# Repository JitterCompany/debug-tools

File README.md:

# Debug Tools for Embedded Development

KiCad projects for the small debug, programming and test boards used across Jitter
projects. Each board has its own folder; manufacturing files are in `production/`.

## Debug adapters

Most Jitter boards expose a single 6-pin
[Würth REDFIT IDC SKEDD](https://www.we-online.com/en/components/products/WST_IDC_PRE_PRESSED_CONNECTOR)
footprint that carries both **SWD and a UART**. SKEDD connectors press straight into
plated holes, so the target board needs no mating connector. The adapters below
convert a debug probe's native header to that 6-pin cable.

| Board | Probe side | Notes |
|---|---|---|
| [BMP-REDFit-adapter](BMP-REDFit-adapter) | Black Magic Probe: standard 10-pin 1.27 mm Arm Cortex Debug header + 4-pin PicoBlade UART | the 10-pin is the common Arm/MIPI-10 JTAG/SWD pinout, so most Cortex probes fit (UART via the separate PicoBlade) |
| [HSprobe-REDFit-adapter](HSprobe-REDFit-adapter) | [hs-probe](https://github.com/probe-rs/hs-probe): 14-pin 1.27 mm STDC14 | STDC14 is ST's STLINK-V3 connector (Arm 10-pin on pins 3–12, UART on 13/14), so STLINK-V3 should fit too |
| [JLink-REDFit-adapter](JLink-REDFit-adapter) | J-Link: standard 20-pin 2.54 mm Arm JTAG header + 4-pin PicoBlade UART | other 20-pin tools give SWD; UART on pins 5/17 is J-Link VCOM specific (else use the PicoBlade) |

### Other adapters

| Board | Purpose |
|---|---|
| [JLink-to-TC2030-IDC__microchip](JLink-to-TC2030-IDC__microchip) | J-Link 20-pin to a Tag-Connect TC2030-IDC with Microchip's pinout |
| [jtag-swd](jtag-swd) | 10-pin Cortex SWD header broken out to 2.54 mm pin headers |

## Misc tools

| Board | Purpose |
|---|---|
| [USBSwitch](USBSwitch) | USB-A / micro-USB passthrough with jumpers to disconnect the data lines and select VBUS from the host or an external 5 V banana-jack supply |

## Factory testers

| Board | Purpose |
|---|---|
| [SL23-modem-tester](SL23-modem-tester) | Test jig for Sensor Link plug-in modules (mini-PCIe LTE modem, SL23 sensor extension) |

## Repository

`libraries/KicadComponents` and `tools/pcb_release` are git submodules
(`git submodule update --init`). Boards are checked and released by the shared KiCad CI
in `.github/workflows`.

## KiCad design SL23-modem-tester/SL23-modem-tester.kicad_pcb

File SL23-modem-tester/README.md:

# SL23 modem tester

A test jig for the modules that plug into a Sensor Link host board. It carries a
mini-PCIe slot for an LTE module, an SL23 extension FFC, and a UI-board connector,
and it ships with factory-test firmware that gives a pass/fail verdict on LEDs plus
a machine-readable log over RTT.

The board is a stripped-down Sensor Link host: same MCU (STM32L4R7), same pinout for
everything a module touches, with the external SRAM and several unrelated parts left
off. That compatibility is deliberate — the test firmware can be proven on a real host
board before any jig exists, and the jig can run ordinary host firmware as a dev board.

## What it tests

| interface | connector | status |
|---|---|---|
| mini-PCIe cellular module | J7 | implemented: rail, AT, SIM, current |
| SL23 extension (23 IO + rails, 30-pin FFC) | J10 | connector present, tests not written |
| UI board | J12 | connector present, tests not written |

**It is not a mini-PCIe tester.** Only the switched 3V3 rail, USART3, `CELLULAR_RESET_n`
/`DTR` and the module's `LED_WWAN` are wired to the slot. The slot's USB pins go only to
the debug header, the PCIe lane is unconnected, and the MCU has no USB host on that side.
It tests *modems that happen to be in mini-PCIe form factor*, over UART.

## Indicators

One red/green pair per zone: the jig itself near the power input, and the module under
test beside its connector. Green blinking means the run is in progress; steady green is
a pass; a blinking red counts out a fault code; a steady red anywhere means the jig
failed its own self-test and no verdict on it can be trusted. Fault codes start at 2 —
a single flash is indistinguishable from a slow blink.

## Firmware

The factory test lives with the firmware, not here. It reads the board revision straps
so one image runs on both this jig and a Sensor Link host board.

## CI

Checked by the shared `pcb_release` gates (`erc`, `drc`, `3d`, `drift`, `pinmap`) —
see `../CI-STATUS.md`. Regenerate the pin map with `tools/pcb.sh pinmap SL23-modem-tester`
after any MCU pin change and commit `pinmap.toml`; the gate diffs against it, so firmware
sees pin changes in review.

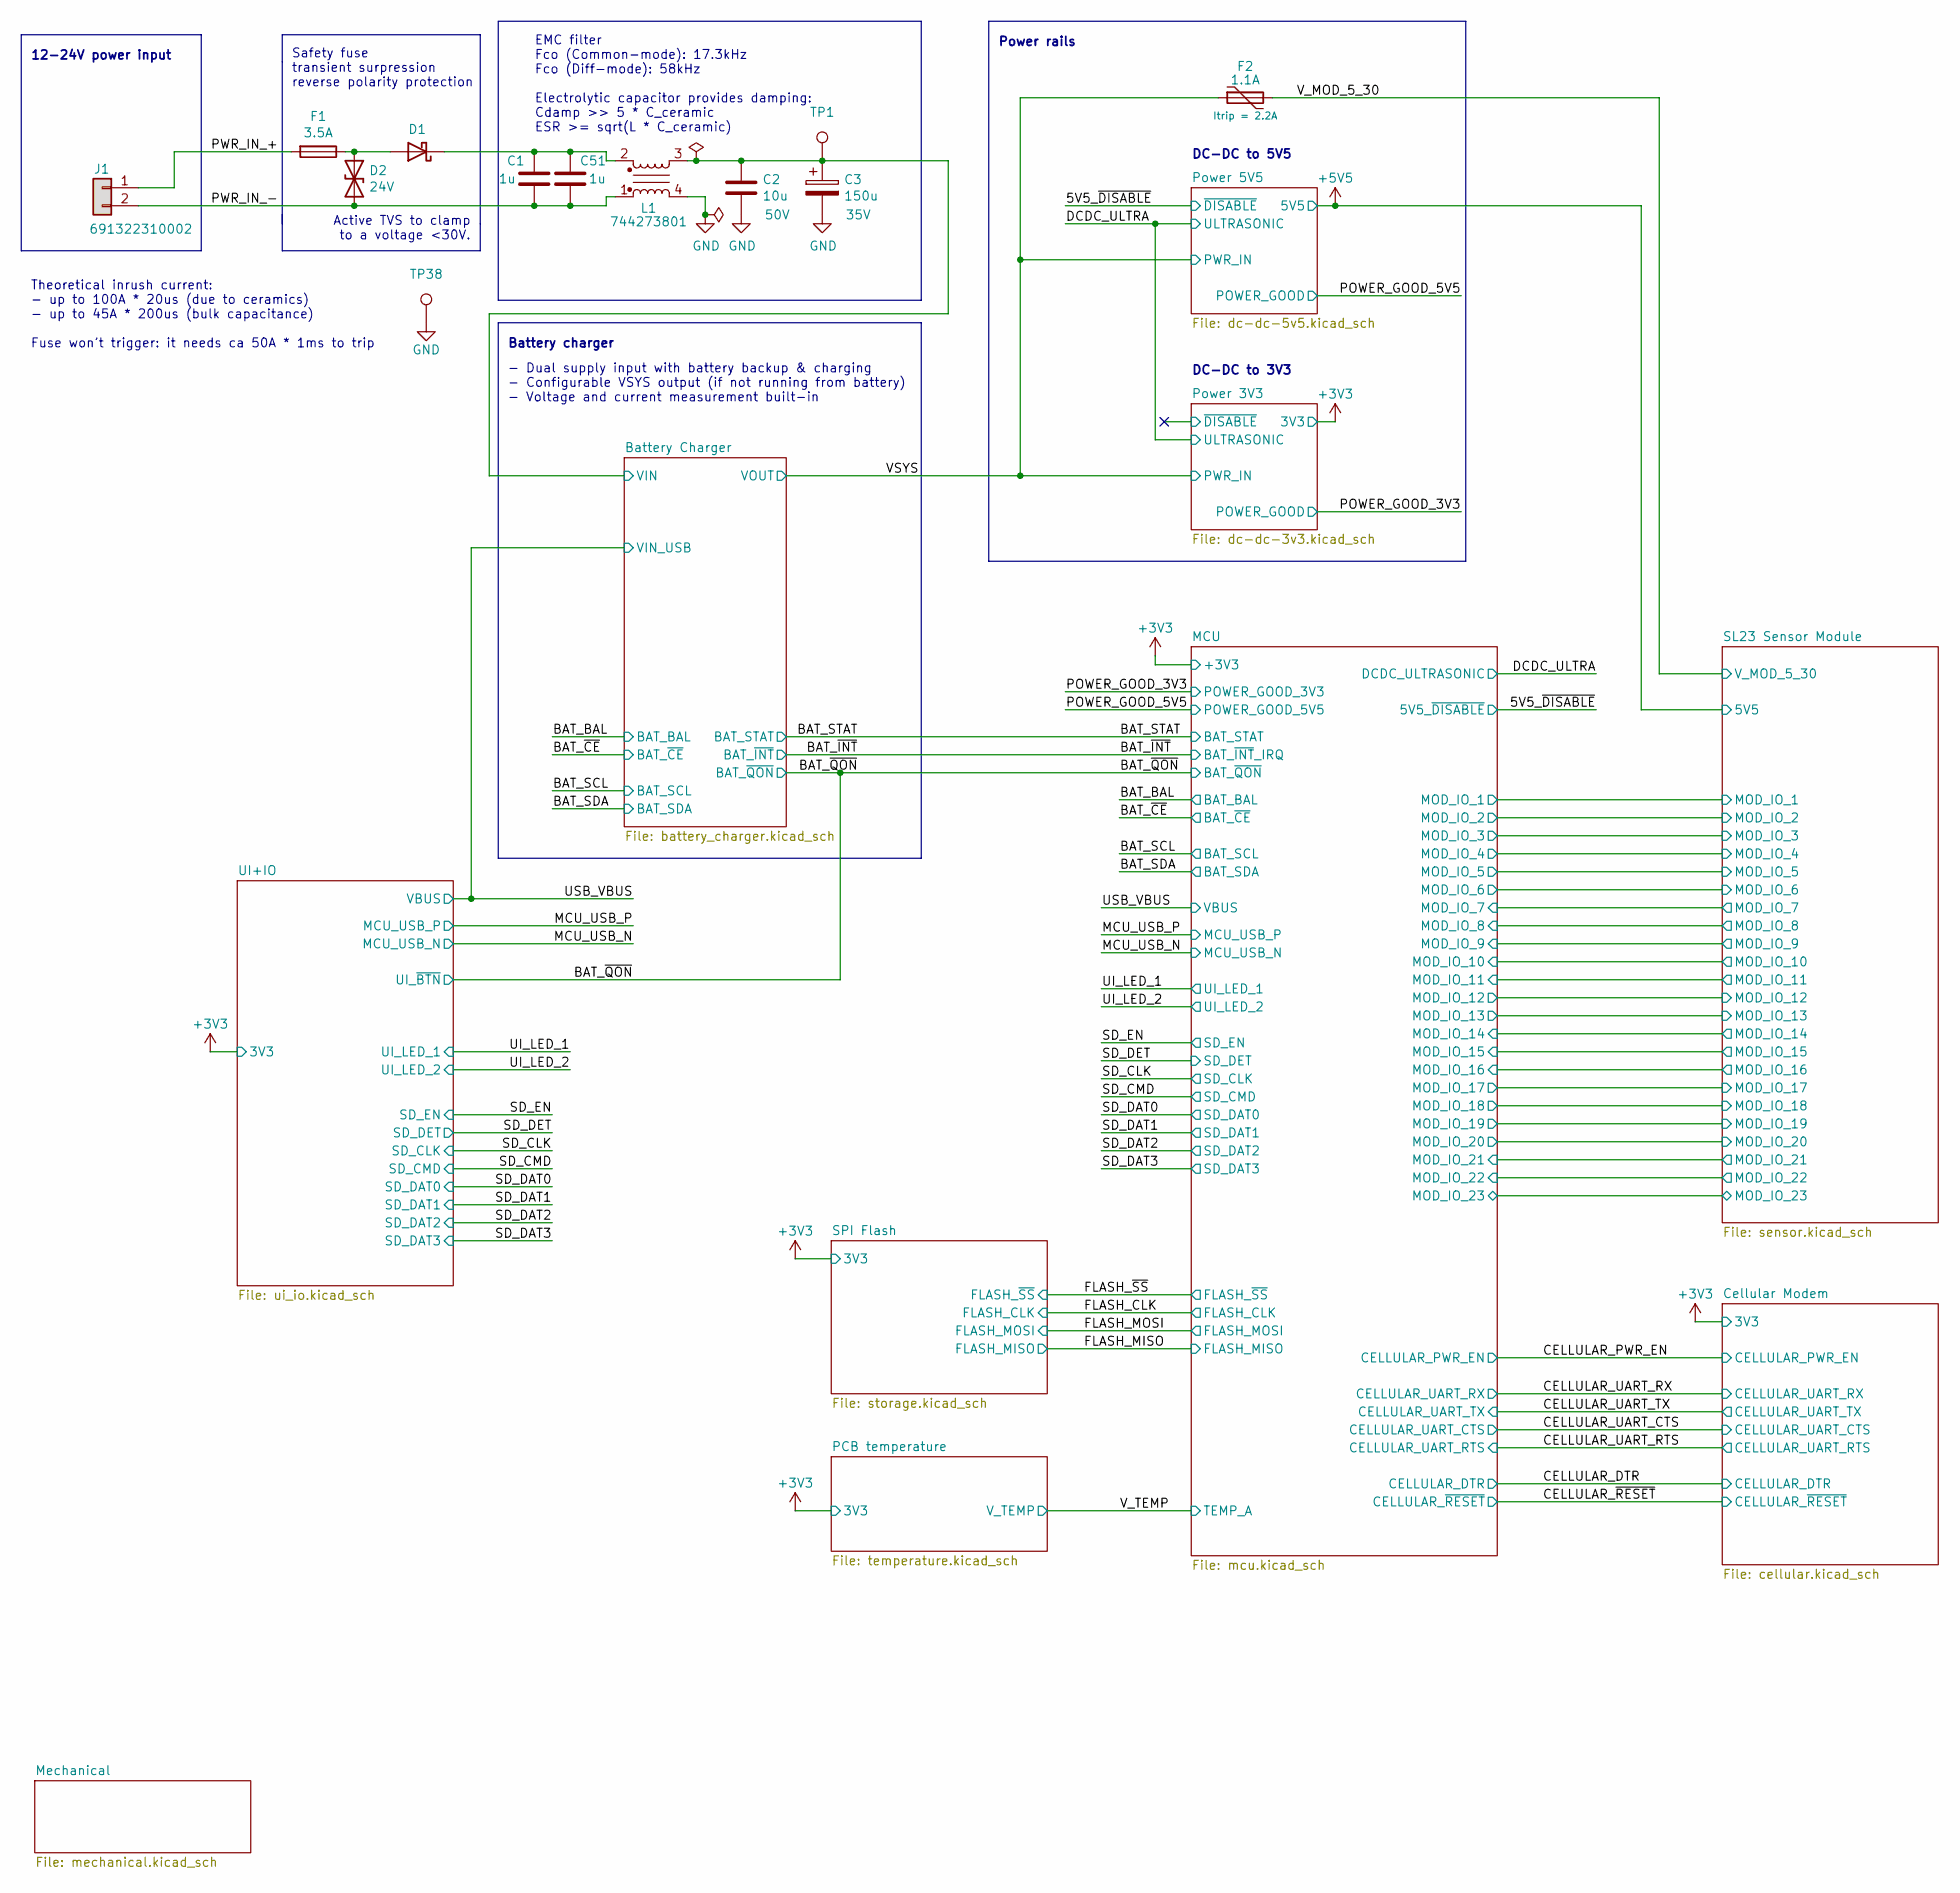
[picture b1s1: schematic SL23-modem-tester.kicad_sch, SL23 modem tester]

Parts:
C1, C51: 1u; C_0603_1608Metric; rating 35V; MPN CGA3E1X7R1V105K080AC; Mouser 810-CGA3E1X7R1V105KC
C2: 10u; C_1210_3225Metric; rating 50V; MPN CL32A106KBJNNNE; Mouser 187-CL32A106KBJNNNE
C3: 150u; CP_Elec_8x10.5_wurth_WCAP_ASLI; rating 35V; MPN 865080553013; Mouser 710-865080553013
D1: PMEG40T30ER; D_SOD-123F; MPN PMEG40T30ER; Mouser 771-PMEG40T30ERX
D2: 24V; D_SMC; MPN XMC7K24CA-M3/H; Mouser 78-XMC7K24CA-M3/H
F1: 3.5A; Fuse_1206_3216Metric; MPN CC12H3.5A-TR; Mouser 504-CC12H3.5A-TR
F2: 1.1A; Fuse_2920; rating Itrip = 2.2A; MPN 2920L100; Mouser 576-2920L100
J1: 691322310002; TerminalBlock_Wurth_WR-TBL_691322310002_1x02_P3.81mm_Horizo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; MPN 691322310002; Mouser 502-L712RAS
L1: 744273801; L_CommonModeChoke_Wuerth_WE-SL5-HC; MPN 744273801; Mouser 710-744273801
TP1, TP38: TestPoint; TestPoint_THTPad_D1.0mm_Drill0.5mm

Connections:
/Battery Charger/VIN: C2.1, C3.1, L1.3, TP1.1 (1_1); also elsewhere on the board
/PWR_IN_+: F1.2, J1.1
/PWR_IN_-: C1.1, C51.1, D2.2 (A2), J1.2, L1.1
/VSYS: F2.1; also elsewhere on the board
/V_MOD_5_30: F2.2; also elsewhere on the board
GND: C2.2, C3.2, L1.4, TP38.1 (1_1); also elsewhere on the board
unnamed: D1.2 (A), D2.1 (A1), F1.1
unnamed: C1.2, C51.2, D1.1 (K), L1.2

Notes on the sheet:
12-24V power input
DC-DC to 3V3
Power rails
EMC filter Fco (Common-mode): 17.3kHz Fco (Diff-mode): 58kHz Electrolytic capacitor provides damping: Cdamp >> 5 * C_ceramic ESR >= sqrt(L * C_ceramic)
Battery charger
Safety fuse transient surpression reverse polarity protection
Theoretical inrush current: - up to 100A * 20us (due to ceramics) - up to 45A * 200us (bulk capacitance) Fuse won't trigger: it needs ca 50A * 1ms to trip
DC-DC to 5V5
Active TVS to clamp to a voltage <30V.
- Dual supply input with battery backup & charging - Configurable VSYS output (if not running from battery) - Voltage and current measurement built-in

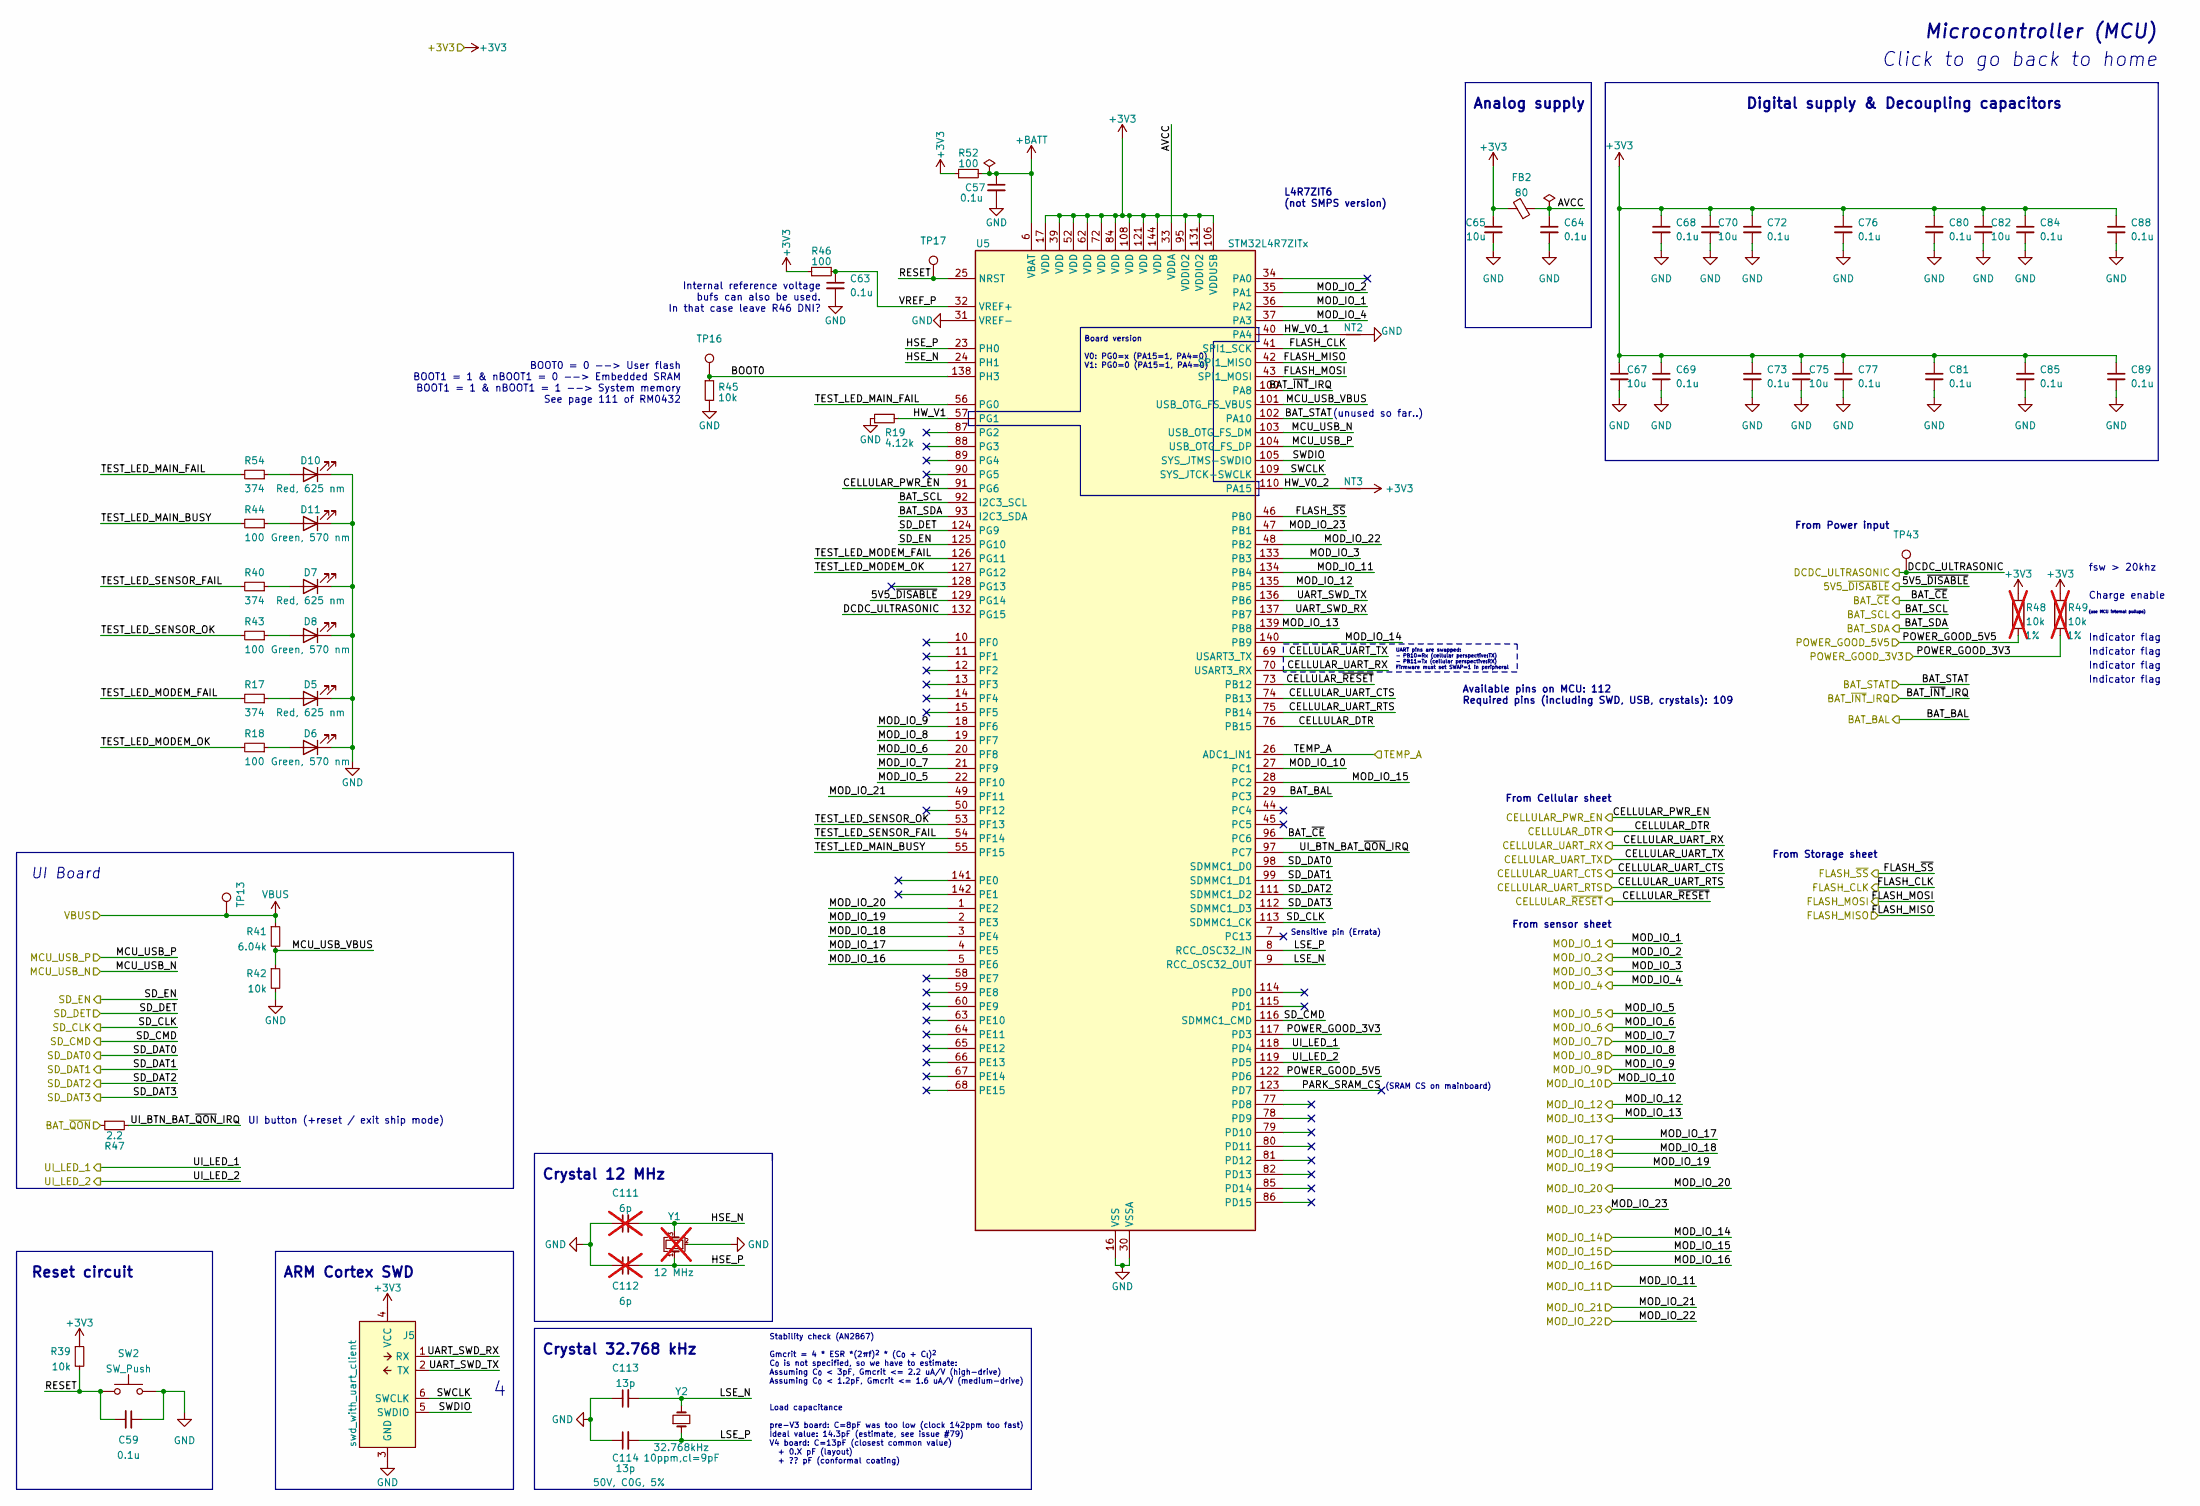
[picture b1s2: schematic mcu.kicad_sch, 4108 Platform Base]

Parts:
C57, C59, C63, C64, C68, C69, C72, C73, C76, C77, C80, C81, C84, C85, C88, C89: 0.1u; C_0603_1608Metric; rating 50V; MPN CGA3E2X7R1H104K080AA; Mouser 810-CGA3E2X7R1H104K
C65, C67, C70, C75, C82: 10u; C_0805_2012Metric; rating 10V
C111, C112: 6p; C_0402_1005Metric; rating 50V; MPN CGA2B2NP01H060D050BA; Mouser 810-CGA2B2NP01H060DA; not fitted
C113, C114: 13p; C_0402_1005Metric; rating 50V, C0G, 5%; MPN GCM1555C1H130JA16D; Mouser 81-GCM1555C1H130JA6D
D5, D7, D10: Red, 625 nm; LED_0603_1608Metric; MPN 150060RS75000; Mouser 710-150060RS75000
D6, D8, D11: Green, 570 nm; LED_0603_1608Metric; MPN 150060VS75000; Mouser 710-150060VS75000
FB2: 80; L_0603_1608Metric; MPN 74279261; Mouser 710-74279261
J5: swd_with_uart_client; WR-WST_REDFIT-6-pins_490107670612
NT2, NT3: NetTie_2; NetTie-2_SMD_Pad0.2mm
R17, R40, R54: 374; R_0603_1608Metric; rating 1%; MPN CRCW0603374RFKEA; Mouser 71-CRCW0603-374-E3
R18, R43, R44, R46, R52: 100; R_0603_1608Metric; rating 1%; MPN CRCW0603100RFKEAC; Mouser 71-CRCW0603100RFKEAC
R19: 4.12k; R_0603_1608Metric; rating 1%
R39, R42, R45: 10k; R_0603_1608Metric; rating 1%; MPN CRCW060310K0FKEAHP; Mouser 71-CRCW060310K0FKEAH
R41: 6.04k; R_0603_1608Metric; rating 1%; MPN CRCW06036K04FKEAC; Mouser 71-CRCW06036K04FKEAC
R47: 2.2; R_0603_1608Metric; rating 1%
R48, R49: 10k; R_0603_1608Metric; rating 1%; MPN CRCW060310K0FKEAHP; Mouser 71-CRCW060310K0FKEAH; not fitted
SW2: SW_Push; C&K_KMR7_button; MPN KMR731NG LFS; Mouser 611-KMR731NGLFS
TP13, TP16, TP17, TP43: TestPoint; TestPoint_THTPad_D1.0mm_Drill0.5mm
U5: STM32L4R7ZITx; LQFP-144_20x20mm_P0.5mm; MPN STM32L4R7ZIT6; Mouser 511-STM32L4R7ZIT6
Y1: 12 MHz; Crystal_SMD_2520-4Pin_2.5x2.0mm; MPN ABM10-167-12.000MHZ-T3; Mouser 815-ABM10-167-12T; not fitted
Y2: 32.768kHz; Crystal_SMD_ABS06-2Pin_2.0x1.2mm; rating 10ppm,cl=9pF; MPN ABS06-32.768KHZ-9-1-T; Mouser 815-ABS06-32.7K-9-T

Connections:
+3V3: C65.1, C67.1, C68.1, C69.1, C70.1, C72.1, C73.1, C75.1, C76.1, C77.1, C80.1, C81.1, C82.1, C84.1, C85.1, C88.1, C89.1, FB2.2, J5.4 (VCC), NT3.2, R39.1, R46.1, R48.1, R49.1, R52.1, U5.17 (VDD), U5.39 (VDD), U5.52 (VDD), U5.62 (VDD), U5.72 (VDD), U5.84 (VDD), U5.95 (VDDIO2), U5.106 (VDDUSB), U5.108 (VDD), U5.121 (VDD), U5.131 (VDDIO2), U5.144 (VDD); also elsewhere on the board
+BATT: C57.1, R52.2, U5.6 (VBAT)
/5V5_~DISABLE: U5.129 (PG14); also elsewhere on the board
/BAT_BAL: U5.29 (PC3); also elsewhere on the board
/BAT_SCL: U5.92 (I2C3_SCL); also elsewhere on the board
/BAT_SDA: U5.93 (I2C3_SDA); also elsewhere on the board
/BAT_STAT: U5.102 (PA10); also elsewhere on the board
/BAT_~CE: U5.96 (PC6); also elsewhere on the board
/BAT_~INT: U5.100 (PA8); also elsewhere on the board
/BAT_~QON: R47.1; also elsewhere on the board
/CELLULAR_DTR: U5.76 (PB15); also elsewhere on the board
/CELLULAR_PWR_EN: U5.91 (PG6); also elsewhere on the board
/CELLULAR_UART_CTS: U5.74 (PB13); also elsewhere on the board
/CELLULAR_UART_RTS: U5.75 (PB14); also elsewhere on the board
/CELLULAR_UART_RX: U5.70 (USART3_RX); also elsewhere on the board
/CELLULAR_UART_TX: U5.69 (USART3_TX); also elsewhere on the board
/CELLULAR_~RESET: U5.73 (PB12); also elsewhere on the board
/DCDC_ULTRA: TP43.1 (1_1), U5.132 (PG15); also elsewhere on the board
/FLASH_CLK: U5.41 (SPI1_SCK); also elsewhere on the board
/FLASH_MISO: U5.42 (SPI1_MISO); also elsewhere on the board
/FLASH_MOSI: U5.43 (SPI1_MOSI); also elsewhere on the board
/FLASH_~SS: U5.46 (PB0); also elsewhere on the board
/MCU/AVCC: C64.1, FB2.1, U5.33 (VDDA)
/MCU/BOOT0: R45.1, TP16.1 (1_1), U5.138 (PH3)
/MCU/HSE_N: C111.2, U5.24 (PH1), Y1.3
/MCU/HSE_P: C112.2, U5.23 (PH0), Y1.1
/MCU/HW_V0_1: NT2.1, U5.40 (PA4)
/MCU/HW_V0_2: NT3.1, U5.110 (PA15)
/MCU/HW_V1: R19.2, U5.57 (PG1)
/MCU/LSE_N: C113.2, U5.9 (RCC_OSC32_OUT), Y2.2
/MCU/LSE_P: C114.2, U5.8 (RCC_OSC32_IN), Y2.1
/MCU/MCU_USB_VBUS: R41.2, R42.1, U5.101 (USB_OTG_FS_VBUS)
/MCU/MOD_IO_1: U5.36 (PA2); also elsewhere on the board
/MCU/MOD_IO_2: U5.35 (PA1); also elsewhere on the board
/MCU/MOD_IO_3: U5.133 (PB3); also elsewhere on the board
/MCU/MOD_IO_4: U5.37 (PA3); also elsewhere on the board
/MCU/MOD_IO_5: U5.22 (PF10); also elsewhere on the board
/MCU/MOD_IO_6: U5.20 (PF8); also elsewhere on the board
/MCU/MOD_IO_7: U5.21 (PF9); also elsewhere on the board
/MCU/MOD_IO_8: U5.19 (PF7); also elsewhere on the board
/MCU/MOD_IO_9: U5.18 (PF6); also elsewhere on the board
/MCU/MOD_IO_10: U5.27 (PC1); also elsewhere on the board
/MCU/MOD_IO_11: U5.134 (PB4); also elsewhere on the board
/MCU/MOD_IO_12: U5.135 (PB5); also elsewhere on the board
/MCU/MOD_IO_13: U5.139 (PB8); also elsewhere on the board
/MCU/MOD_IO_14: U5.140 (PB9); also elsewhere on the board
/MCU/MOD_IO_15: U5.28 (PC2); also elsewhere on the board
/MCU/MOD_IO_16: U5.5 (PE6); also elsewhere on the board
/MCU/MOD_IO_17: U5.4 (PE5); also elsewhere on the board
/MCU/MOD_IO_18: U5.3 (PE4); also elsewhere on the board
/MCU/MOD_IO_19: U5.2 (PE3); also elsewhere on the board
/MCU/MOD_IO_20: U5.1 (PE2); also elsewhere on the board
/MCU/MOD_IO_21: U5.49 (PF11); also elsewhere on the board
/MCU/MOD_IO_22: U5.48 (PB2); also elsewhere on the board
/MCU/MOD_IO_23: U5.47 (PB1); also elsewhere on the board
/MCU/PARK_SRAM_CS: U5.123 (PD7)
/MCU/RESET: C59.2, R39.2, SW2.2, TP17.1 (1_1), U5.25 (NRST)
/MCU/SWCLK: J5.6 (SWCLK), U5.109 (SYS_JTCK-SWCLK)
/MCU/SWDIO: J5.5 (SWDIO), U5.105 (SYS_JTMS-SWDIO)
/MCU/TEST_LED_MAIN_BUSY: R44.2, U5.55 (PF15)
/MCU/TEST_LED_MAIN_FAIL: R54.2, U5.56 (PG0)
/MCU/TEST_LED_MODEM_FAIL: R17.2, U5.126 (PG11)
/MCU/TEST_LED_MODEM_OK: R18.2, U5.127 (PG12)
/MCU/TEST_LED_SENSOR_FAIL: R40.2, U5.54 (PF14)
/MCU/TEST_LED_SENSOR_OK: R43.2, U5.53 (PF13)
/MCU/UART_SWD_RX: J5.1 (RX), U5.137 (PB7)
/MCU/UART_SWD_TX: J5.2 (TX), U5.136 (PB6)
/MCU/UI_BTN_BAT_~QON_IRQ: R47.2, U5.97 (PC7)
/MCU/VREF_P: C63.1, R46.2, U5.32 (VREF+)
/MCU_USB_N: U5.103 (USB_OTG_FS_DM); also elsewhere on the board
/MCU_USB_P: U5.104 (USB_OTG_FS_DP); also elsewhere on the board
/POWER_GOOD_3V3: R49.2, U5.117 (PD3); also elsewhere on the board
/POWER_GOOD_5V5: R48.2, U5.122 (PD6); also elsewhere on the board
/SD_CLK: U5.113 (SDMMC1_CK); also elsewhere on the board
/SD_CMD: U5.116 (SDMMC1_CMD); also elsewhere on the board
/SD_DAT0: U5.98 (SDMMC1_D0); also elsewhere on the board
/SD_DAT1: U5.99 (SDMMC1_D1); also elsewhere on the board
/SD_DAT2: U5.111 (SDMMC1_D2); also elsewhere on the board
/SD_DAT3: U5.112 (SDMMC1_D3); also elsewhere on the board
/SD_DET: U5.124 (PG9); also elsewhere on the board
/SD_EN: U5.125 (PG10); also elsewhere on the board
/UI_LED_1: U5.118 (PD4); also elsewhere on the board
/UI_LED_2: U5.119 (PD5); also elsewhere on the board
/V_TEMP: U5.26 (ADC1_IN1); also elsewhere on the board
GND: C57.2, C59.1, C63.2, C64.2, C65.2, C67.2, C68.2, C69.2, C70.2, C72.2, C73.2, C75.2, C76.2, C77.2, C80.2, C81.2, C82.2, C84.2, C85.2, C88.2, C89.2, C111.1, C112.1, C113.1, C114.1, D5.1 (K), D6.1 (K), D7.1 (K), D8.1 (K), D10.1 (K), D11.1 (K), J5.3 (GND), NT2.2, R19.1, R42.2, R45.2, SW2.1, U5.16 (VSS), U5.30 (VSSA), U5.31 (VREF-), U5.38 (VSS), U5.51 (VSS), U5.61 (VSS), U5.71 (VSS), U5.83 (VSS), U5.94 (VSS), U5.107 (VSS), U5.120 (VSS), U5.130 (VSS), U5.143 (VSS), Y1.2 (G), Y1.4 (G); also elsewhere on the board
unnamed: D5.2 (A), R17.1
unnamed: D6.2 (A), R18.1
unnamed: D7.2 (A), R40.1
unnamed: D8.2 (A), R43.1
unnamed: D10.2 (A), R54.1
unnamed: D11.2 (A), R44.1
VBUS: R41.1, TP13.1 (1_1); also elsewhere on the board

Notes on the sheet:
Indicator flag
UART pins are swapped: - PB10=Rx (cellular perspective:TX) - PB11=Tx (cellular perspective:RX) Firmware must set SWAP=1 in peripheral
UI Board
BOOT0 = 0 --> User flash BOOT1 = 1 & nBOOT1 = 0 --> Embedded SRAM BOOT1 = 1 & nBOOT1 = 1 --> System memory See page 111 of RM0432
Reset circuit
From sensor sheet
Crystal 32.768 kHz
From Cellular sheet
Load capacitance pre-V3 board: C=8pF was too low (clock 142ppm too fast) Ideal value: 14.3pF (estimate, see issue #79) V4 board: C=13pF (closest common value) + 0.X pF (layout) + ?? pF (conformal coating)
Click to go back to home
ARM Cortex SWD
Sensitive pin (Errata)
fsw > 20khz
Microcontroller (MCU)
UI button (+reset / exit ship mode)
Crystal 12 MHz
Internal reference voltage bufs can also be used. In that case leave R46 DNI?
(unused so far..)
From Power input
(use MCU internal pullups)
L4R7ZIT6 (not SMPS version)
Analog supply
Charge enable
From Storage sheet
Digital supply & Decoupling capacitors
Board version V0: PG0=x (PA15=1, PA4=0) V1: PG0=0 (PA15=1, PA4=0)
Stability check (AN2867) Gmcrit = 4 * ESR *(2πf)^{2} * (C_{0} + C_{l})^{2} C_{0} is not specified, so we have to estimate: Assuming C_{0} < 3pF, Gmcrit <= 2.2 uA/V (high-drive) Assuming C_{0} < 1.2pF, Gmcrit <= 1.6 uA/V (medium-drive)
(SRAM CS on mainboard)
Available pins on MCU: 112 Required pins (including SWD, USB, crystals): 109

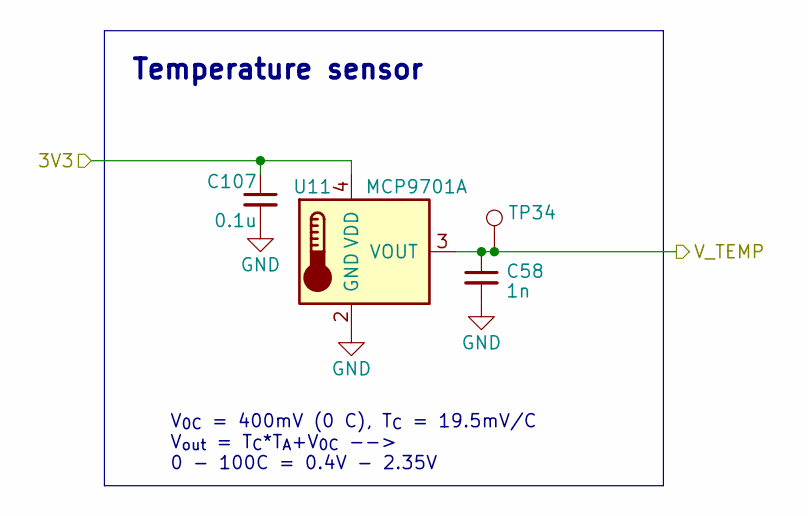
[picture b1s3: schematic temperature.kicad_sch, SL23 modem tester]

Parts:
C58: 1n; C_0603_1608Metric; rating 50V; MPN CGA3E2X7R1H102K080AA; Mouser 810-CGA3E2X7R1H102K
C107: 0.1u; C_0603_1608Metric; rating 50V; MPN CGA3E2X7R1H104K080AA; Mouser 810-CGA3E2X7R1H104K
TP34: TestPoint; TestPoint_THTPad_D1.0mm_Drill0.5mm
U11: MCP9701A; SOT-353_SC-70-5; MPN MCP9701AT-E/LT; Mouser 579-MCP9701AT-E/LT

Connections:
+3V3: C107.1, U11.4 (VDD); also elsewhere on the board
/V_TEMP: C58.1, TP34.1 (1_1), U11.3 (VOUT); also elsewhere on the board
GND: C58.2, C107.2, U11.2 (GND); also elsewhere on the board

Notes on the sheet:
V_{0C} = 400mV (0 C), T_{C} = 19.5mV/C V_{out} = T_{C}*T_{A}+V_{0C} --> 0 - 100C = 0.4V - 2.35V
Temperature sensor

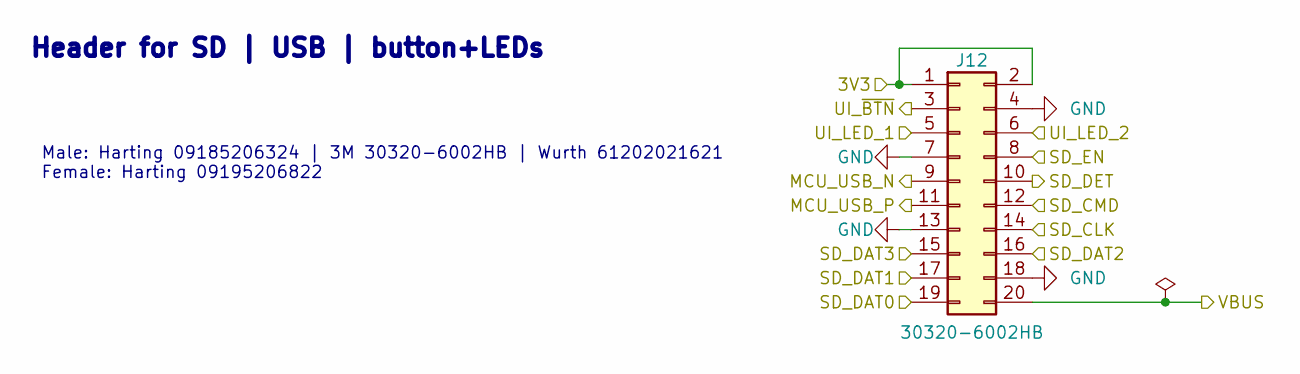
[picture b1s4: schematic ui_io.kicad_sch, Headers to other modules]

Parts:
J12: 30320-6002HB; IDC_Header_2x10_P2.54mm_Vertical_MALE; MPN 30320-6002HB; Mouser 517-30320-6002

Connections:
+3V3: J12.1, J12.2; also elsewhere on the board
/BAT_~QON: J12.3; also elsewhere on the board
/MCU_USB_N: J12.9; also elsewhere on the board
/MCU_USB_P: J12.11; also elsewhere on the board
/SD_CLK: J12.14; also elsewhere on the board
/SD_CMD: J12.12; also elsewhere on the board
/SD_DAT0: J12.19; also elsewhere on the board
/SD_DAT1: J12.17; also elsewhere on the board
/SD_DAT2: J12.16; also elsewhere on the board
/SD_DAT3: J12.15; also elsewhere on the board
/SD_DET: J12.10; also elsewhere on the board
/SD_EN: J12.8; also elsewhere on the board
/UI_LED_1: J12.5; also elsewhere on the board
/UI_LED_2: J12.6; also elsewhere on the board
GND: J12.4, J12.7, J12.13, J12.18; also elsewhere on the board
VBUS: J12.20; also elsewhere on the board

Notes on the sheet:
Male: Harting 09185206324 | 3M 30320-6002HB | Wurth 61202021621 Female: Harting 09195206822
Header for SD | USB | button+LEDs

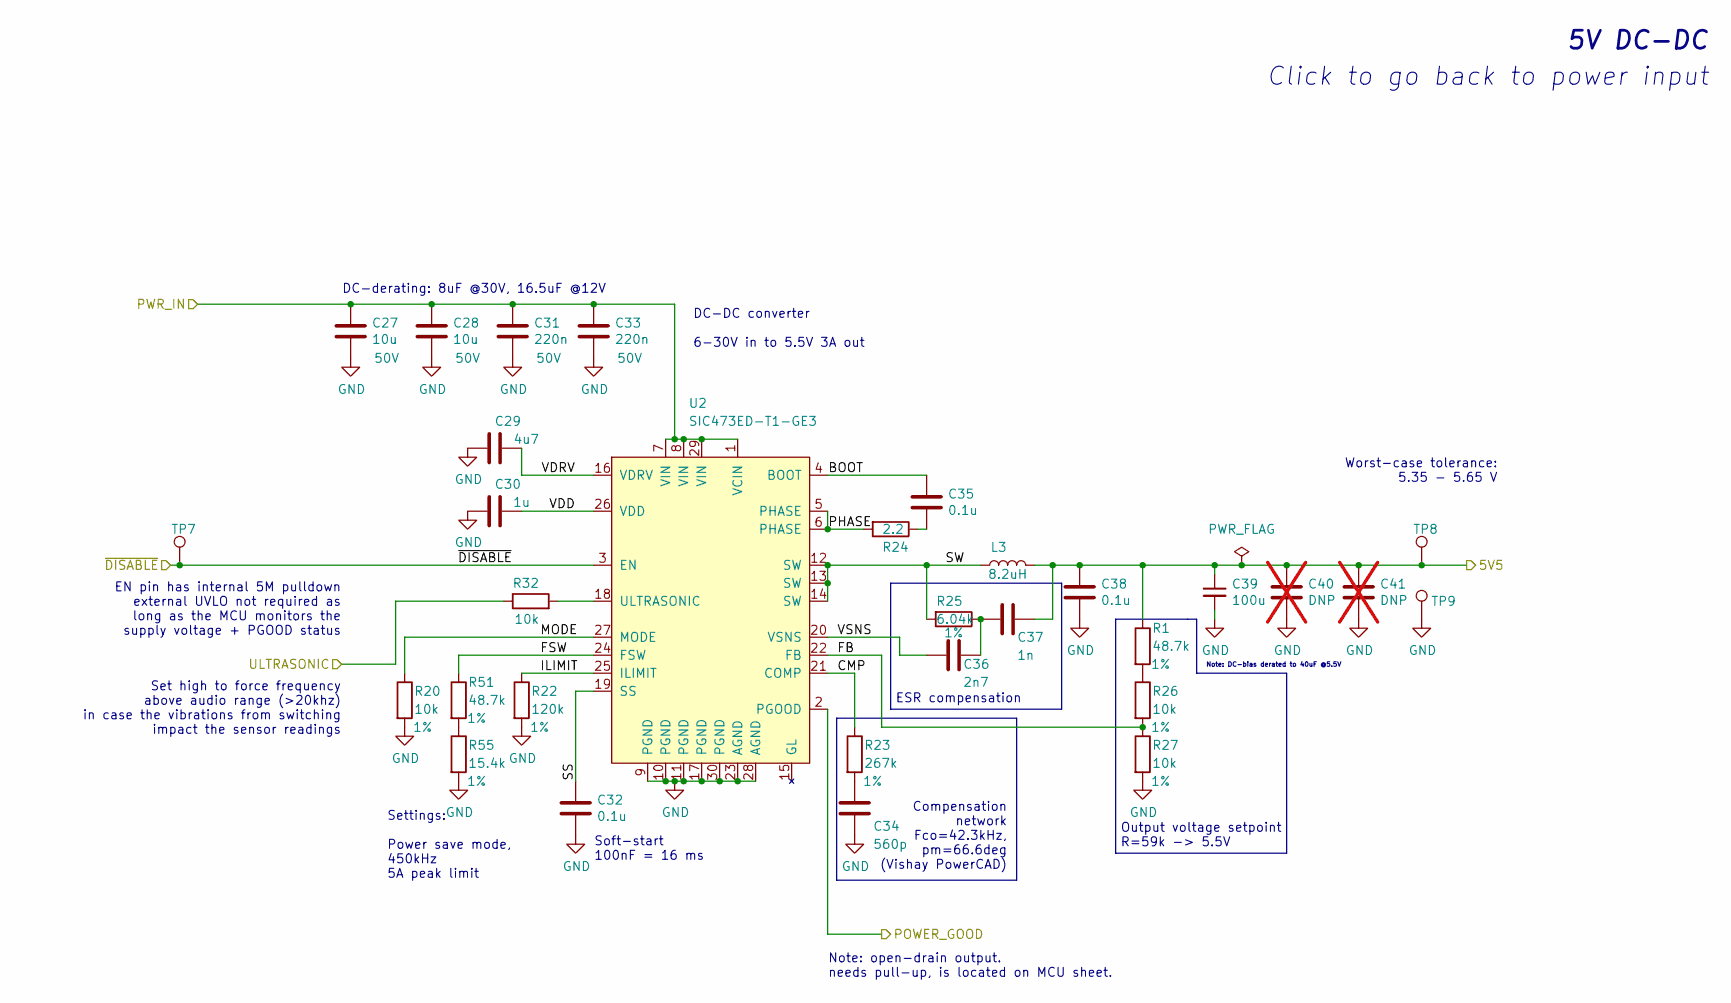
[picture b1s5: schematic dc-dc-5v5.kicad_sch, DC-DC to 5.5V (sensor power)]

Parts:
C27, C28: 10u; C_1210_3225Metric; rating 50V; MPN CL32A106KBJNNNE; Mouser 187-CL32A106KBJNNNE
C29: 4u7; C_0805_2012Metric; rating 50V; MPN GRM21BZ71H475KE15K; Mouser 81-GRM21BZ71H475KE5K
C30: 1u; C_0603_1608Metric; rating 35V; MPN CGA3E1X7R1V105K080AC; Mouser 810-CGA3E1X7R1V105KC
C31, C33: 220n; C_0603_1608Metric; rating 50V; MPN CGA3E3X7R1H224K080AB; Mouser 810-CGA3E3X7R1H224K
C32, C35, C38: 0.1u; C_0603_1608Metric; rating 50V; MPN CGA3E2X7R1H104K080AA; Mouser 810-CGA3E2X7R1H104K
C34: 560p; C_0603_1608Metric; rating 50V; MPN GCM188L81H561KA03D; Mouser 81-GCM188L81H561KA3D
C36: 2n7; C_0603_1608Metric; rating 50V; MPN CGA3E2C0G1H272J080AE; Mouser 810-CGA3E2C0G1H272J8
C37: 1n; C_0603_1608Metric; rating 50V; MPN CGA3E2X7R1H102K080AA; Mouser 810-CGA3E2X7R1H102K
C39: 100u; C_1210_3225Metric; rating 6V3; MPN CL32A107MQVNNNE; Mouser 187-CL32A107MQVNNNE
C40, C41: DNP; C_1210_3225Metric; not fitted
L3: 8.2uH; L_Wuerth_LHMI_8040; MPN 74437358082; Mouser 710-74437358082
R1, R51: 48.7k; R_0603_1608Metric; rating 1%
R20, R26, R27, R32: 10k; R_0603_1608Metric; rating 1%; MPN CRCW060310K0FKEAHP; Mouser 71-CRCW060310K0FKEAH
R22: 120k; R_0603_1608Metric; rating 1%; MPN CRCW0603120KFKEAC; Mouser 71-CRCW0603120KFKEAC
R23: 267k; R_0603_1608Metric; rating 1%; MPN CR0603-FX-2673ELF; Mouser 652-CR0603FX-2673ELF
R24: 2.2; R_0603_1608Metric; rating 1%; MPN CRCW06032R20FKEAC; Mouser 71-CRCW06032R20FKEAC
R25: 6.04k; R_0603_1608Metric; rating 1%; MPN CRCW06036K04FKEAC; Mouser 71-CRCW06036K04FKEAC
R55: 15.4k; R_0603_1608Metric; rating 1%
TP7, TP8, TP9: TestPoint; TestPoint_THTPad_D1.0mm_Drill0.5mm
U2: SIC473ED-T1-GE3; Vishay_MLP55-27L; MPN SIC473ED-T1-GE3; Mouser 78-SIC473ED-T1-GE3

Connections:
+5V5: C37.1, C38.1, C39.1, C40.1, C41.1, L3.2, R1.1, TP8.1 (1_1); also elsewhere on the board
/5V5_~DISABLE: TP7.1 (1_1), U2.3 (EN); also elsewhere on the board
/DCDC_ULTRA: R32.1; also elsewhere on the board
/POWER_GOOD_5V5: U2.2 (PGOOD); also elsewhere on the board
/Power 5V5/BOOT: C35.1, U2.4 (BOOT)
/Power 5V5/CMP: R23.1, U2.21 (COMP)
/Power 5V5/FB: R26.2, R27.1, U2.22 (FB)
/Power 5V5/FSW: R51.1, U2.24 (FSW)
/Power 5V5/ILIMIT: R22.1, U2.25 (ILIMIT)
/Power 5V5/MODE: R20.1, U2.27 (MODE)
/Power 5V5/PHASE: R24.2, U2.5 (PHASE), U2.6 (PHASE)
/Power 5V5/SS: C32.1, U2.19 (SS)
/Power 5V5/SW: L3.1, R25.2, U2.12 (SW), U2.13 (SW), U2.14 (SW)
/Power 5V5/VDD: C30.2, U2.26 (VDD)
/Power 5V5/VDRV: C29.2, U2.16 (VDRV)
/Power 5V5/VSNS: C36.2, U2.20 (VSNS)
/VSYS: C27.1, C28.1, C31.1, C33.1, U2.1 (VCIN), U2.7 (VIN), U2.8 (VIN), U2.29 (VIN); also elsewhere on the board
GND: C27.2, C28.2, C29.1, C30.1, C31.2, C32.2, C33.2, C34.2, C38.2, C39.2, C40.2, C41.2, R20.2, R22.2, R27.2, R55.2, TP9.1 (1_1), U2.9 (PGND), U2.10 (PGND), U2.11 (PGND), U2.17 (PGND), U2.23 (AGND), U2.28 (AGND), U2.30 (PGND); also elsewhere on the board
unnamed: C34.1, R23.2
unnamed: C35.2, R24.1
unnamed: C36.1, C37.2, R25.1
unnamed: R1.2, R26.1
unnamed: R51.2, R55.1
unnamed: R32.2, U2.18 (ULTRASONIC)

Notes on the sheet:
Compensation network Fco=42.3kHz, pm=66.6deg (Vishay PowerCAD)
Note: open-drain output. needs pull-up, is located on MCU sheet.
5V DC-DC
Set high to force frequency above audio range (>20khz) in case the vibrations from switching impact the sensor readings
Settings: Power save mode, 450kHz 5A peak limit
DC-derating: 8uF @30V, 16.5uF @12V
Worst-case tolerance: 5.35 - 5.65 V
EN pin has internal 5M pulldown external UVLO not required as long as the MCU monitors the supply voltage + PGOOD status
ESR compensation
Soft-start 100nF = 16 ms
DC-DC converter 6-30V in to 5.5V 3A out
Click to go back to power input
Output voltage setpoint R=59k -> 5.5V
Note: DC-bias derated to 40uF @5.5V

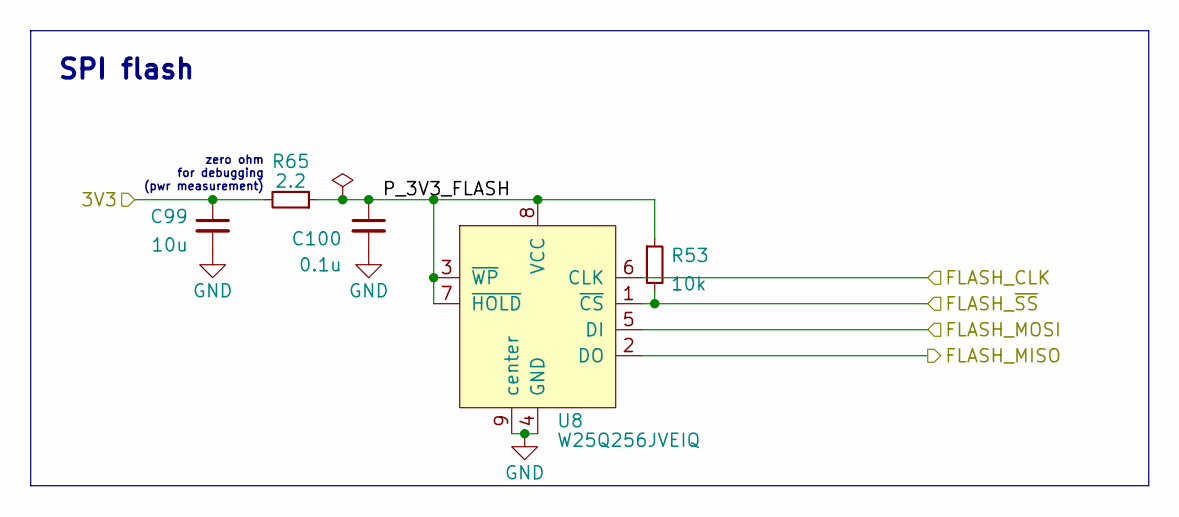
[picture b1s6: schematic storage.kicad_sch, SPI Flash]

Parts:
C99: 10u; C_0805_2012Metric; rating 10V
C100: 0.1u; C_0603_1608Metric; rating 50V; MPN CGA3E2X7R1H104K080AA; Mouser 810-CGA3E2X7R1H104K
R53: 10k; R_0603_1608Metric
R65: 2.2; R_0603_1608Metric; rating 1%
U8: W25Q256JVEIQ; WSON-8-1EP_8x6mm_P1.27mm_EP3.4x4.3mm; MPN W25Q256JVEIQ; Mouser 454-W25Q256JVEIQ

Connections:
+3V3: C99.1, R65.2; also elsewhere on the board
/FLASH_CLK: U8.6 (CLK); also elsewhere on the board
/FLASH_MISO: U8.2 (DO); also elsewhere on the board
/FLASH_MOSI: U8.5 (DI); also elsewhere on the board
/FLASH_~SS: R53.2, U8.1 (~CS); also elsewhere on the board
/SPI Flash/P_3V3_FLASH: C100.1, R53.1, R65.1, U8.3 (~WP), U8.7 (~HOLD), U8.8 (VCC)
GND: C99.2, C100.2, U8.4 (GND), U8.9 (center); also elsewhere on the board

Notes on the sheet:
SPI flash
zero ohm for debugging (pwr measurement)
